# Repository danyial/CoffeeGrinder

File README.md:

# CoffeeGrinder

**Smart coffee grinder controller** with MQTT, OTA updates, and full Home Assistant integration.  
Includes 3D-printable housing, custom PCB (KiCad), and open-source firmware for ESP32.

---

## ✨ Features

- ☕️ Weight-based preset grinding
- 📡 MQTT auto-discovery (Home Assistant integration)
- 🌐 Web interface for configuration
- 🔧 Touch buttons for presets and calibration
- 📊 Live sensor telemetry and control
- 📦 STL files for 3D-printed case
- 🔌 KiCad schematics and PCB

---

## ⚙️ Cycloidal Drive (WIP)

This project uses a custom 3D-printed **cycloidal drive** to reduce the stepper motor's speed and increase torque.  
Currently, this mechanism is still under testing and may change in future iterations.

Contributions, feedback, and test results are welcome!

## 🖼️ Images

<p align="center">
  
  <br/>
  <em>CoffeeGrinder assembled</em>
</p>

<p align="center">
  
  <br/>
  <em>Section view (sliced)</em>
</p>

<p align="center">
  
  <br/>
  <em>Cycloidal Drive Top View</em>
</p>

<p align="center">
  
  <br/>
  <em>Cycloidal Drive Bottom View</em>
</p>

<p align="center">
  
  <br/>
  <em>Cycloidal Drive Sliced View</em>
</p>

<p align="center">

  <br/>
  <em>Home Assistant</em>
</p>

---

## 📁 Project Structure

```text
CoffeeGrinder/
├── src/                # Firmware source code
├── include/            # Header files
├── lib/                # Custom libraries (optional)
├── data/               # Web interface (SPIFFS)
├── hardware/
│   ├── stl/            # 3D-printable case parts
│   ├── kicad/          # KiCad PCB project
│   ├── images/         # Project images
│   └── docs/           # Rendered schematics (PDF)
├── docs/               # General project documentation
├── LICENSE.md          # License (AGPL + CC BY-NC-SA)
└── README.md           # This file
```

---

## 🚀 Getting Started

## 🧾 Bill of Materials (BOM)

> **Note**: Some of the links below are affiliate links. If you make a purchase through them, I may receive a small commission at no extra cost to you. Thank you for your support!

- Manual Coffee Grinder [🛒 Amazon](https://amzn.to/4o6IfON)
- ESP32 Dev Board [🛒 Amazon](https://amzn.to/40CVtJ8)
- OLED Display [🛒 Amazon](https://amzn.to/44N8UZx)
- Step Down Converter [🛒 Amazon](https://amzn.to/4o4rhAz)
- HX711 Weight Sensor [🛒 Amazon](https://amzn.to/4lEH1bS)
- Scale [🛒 Amazon](https://amzn.to/3Uswbtt)
- 3x TTP223 Touch Sensors [🛒 Amazon](https://amzn.to/4133kje)
- 3x 10nF Capacitors [🛒 Amazon](https://amzn.to/3IF0UBf)
- Brushless Motor 5010 360KV [🛒 Amazon](https://amzn.to/3VFhHHp)
- ESC 35A or similar (BLHeli_s) - any ESC for brushless motors should work [🛒 Amazon](https://amzn.to/4mAlXCX)
- 2x Bearing 30x37x4 [🛒 Amazon](https://amzn.to/46XXUtu)
- 2x Bearing 8x12x3.5 [🛒 Amazon](https://amzn.to/3UtORsR)
- 2x Bearing 7x13x4 [🛒 Amazon](https://amzn.to/470tUxc)
- 6x Spacer [🛒 Amazon](https://amzn.to/4lLxm3v)
- 12x Magnets 7x2 [🛒 Amazon](https://amzn.to/4f6ZivV)
- Power Supply [🛒 Amazon](https://amzn.to/4o3DJ3y)
- Elko [🛒 Amazon](https://amzn.to/3Uhur6B)
- DC Connector [🛒 Amazon](https://amzn.to/4f7ja2e)
- some cables
- 2x M3x12 SHCS screws [🛒 Amazon](https://amzn.to/4lT12eP)
- 6x M3x16 SHCS screws [🛒 Amazon](https://amzn.to/4lT12eP)
- 6x M3x25 SHCS screws [🛒 Amazon](https://amzn.to/4lT12eP)
- 10x M3x30 SHCS screws [🛒 Amazon](https://amzn.to/4lT12eP)
- 10x M3 screws [🛒 Amazon](https://amzn.to/44Lvy4o)
- 8x M3 nuts [🛒 Amazon](https://amzn.to/4lT12eP)
- 2x M4x20 SHCS screws [🛒 Amazon](https://amzn.to/4lILPgh)
- 6x M3 Threaded Inserts [🛒 Amazon](https://amzn.to/474Kj3K)
- 2x M4 Threaded Inserts [🛒 Amazon](https://amzn.to/44OBxFI)

### Requirements

- MQTT Broker (e.g., Mosquitto)
- Home Assistant (optional, for integration)

### Flashing

Use [PlatformIO](https://platformio.org/) in VSCode:

---

## 🔧 Web Interface

Accessible after WiFi configuration.  
Use it to set:

- MQTT server credentials
- Calibration
- Preset values
- Start grinding manually

---

## 🧠 Home Assistant Integration

Entities auto-discovered via MQTT:

- Sensors: weight, selected preset, scale factor, total weight
- Numbers: block threshold, preset weights
- Buttons: start, calibrate, tare, run preset

Make sure `discovery` is enabled in your MQTT integration.

---

## 🔐 License

- Firmware: [AGPL-3.0](https://www.gnu.org/licenses/agpl-3.0.html)
- Hardware + STL: [CC BY-NC-SA 4.0](https://creativecommons.org/licenses/by-nc-sa/4.0/)

**© 2025 Danny Smolinsky**

For commercial licensing inquiries, contact the author.

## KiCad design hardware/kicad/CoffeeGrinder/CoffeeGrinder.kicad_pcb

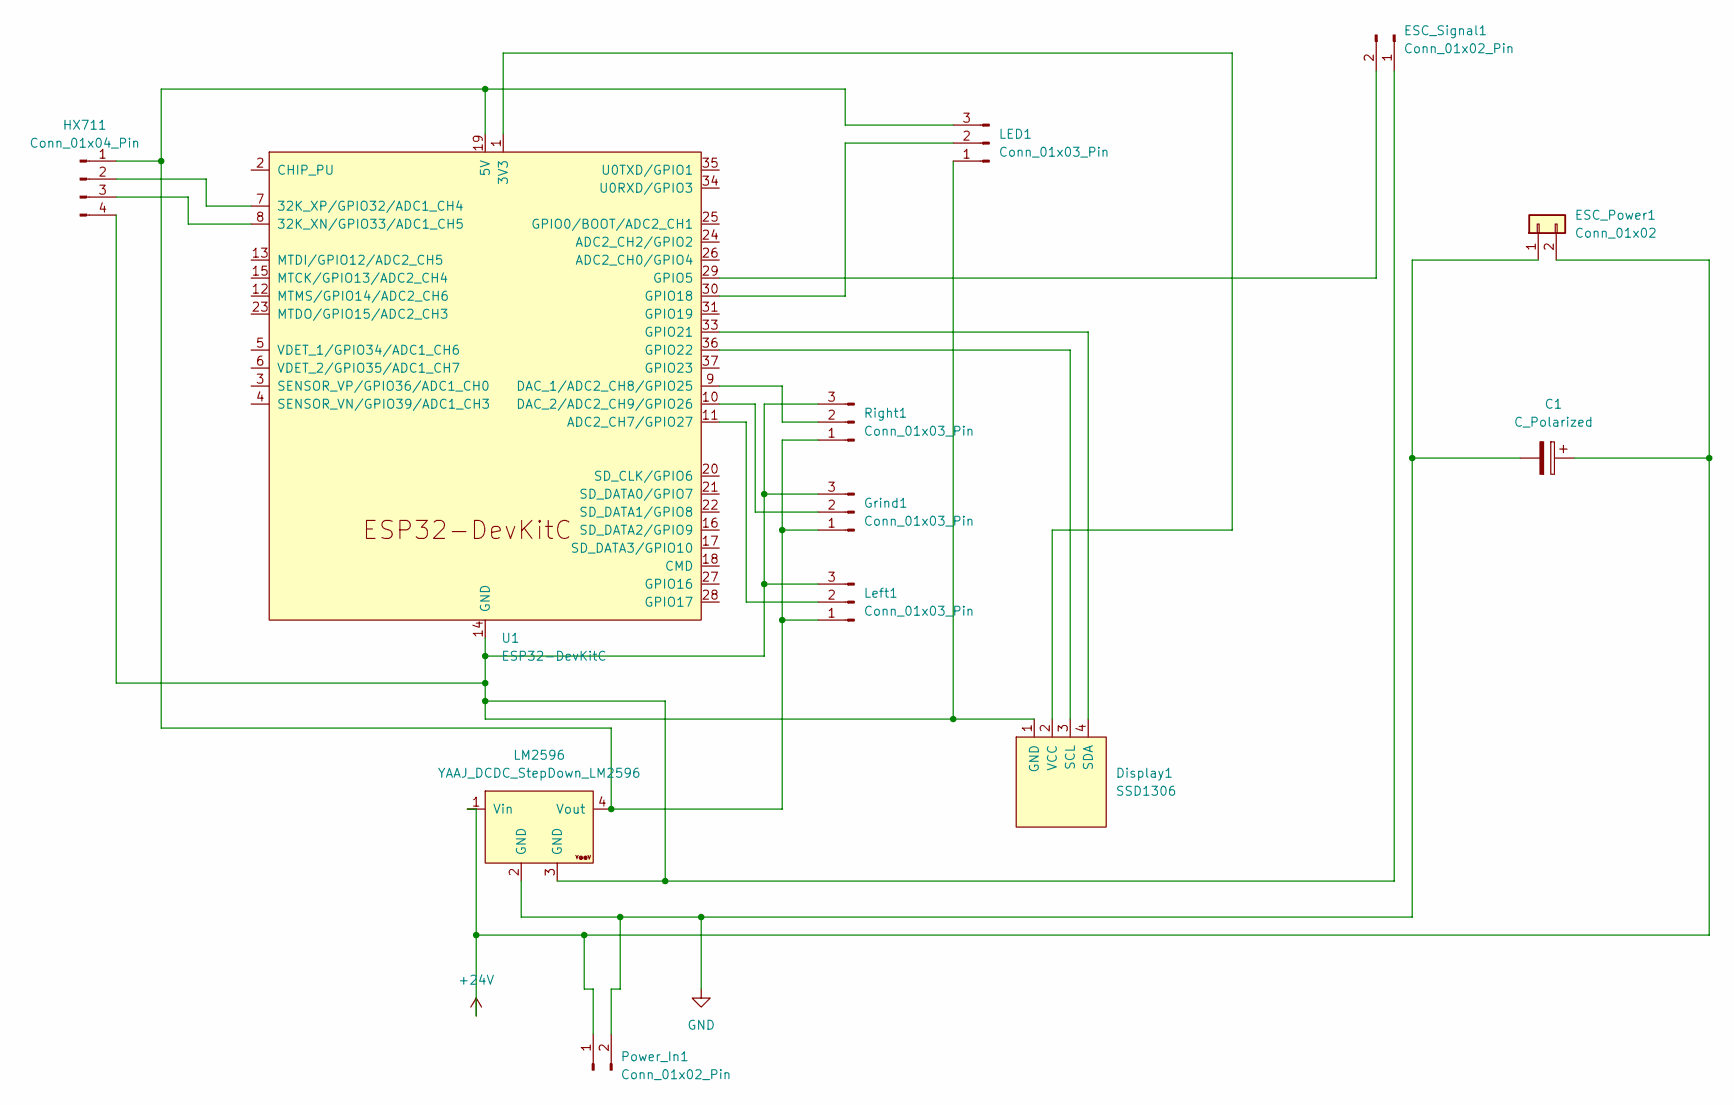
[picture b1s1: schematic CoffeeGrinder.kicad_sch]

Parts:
C1: C_Polarized; CP_Radial_D10.0mm_P7.50mm
Display1: SSD1306; JST_PH_B4B-PH-K_1x04_P2.00mm_Vertical
ESC_Power1: Conn_01x02; AMASS_XT30UPB-F_1x02_P5.0mm_Vertical
ESC_Signal1: Conn_01x02_Pin; JST_PH_B2B-PH-K_1x02_P2.00mm_Vertical
Grind1: Conn_01x03_Pin; JST_PH_B3B-PH-K_1x03_P2.00mm_Vertical
HX711: Conn_01x04_Pin; JST_PH_B4B-PH-K_1x04_P2.00mm_Vertical
LED1: Conn_01x03_Pin; JST_PH_B3B-PH-K_1x03_P2.00mm_Vertical
LM2596: YAAJ_DCDC_StepDown_LM2596
Left1: Conn_01x03_Pin; JST_PH_B3B-PH-K_1x03_P2.00mm_Vertical
Power_In1: Conn_01x02_Pin; AMASS_XT30UPB-M_1x02_P5.0mm_Vertical
Right1: Conn_01x03_Pin; JST_PH_B3B-PH-K_1x03_P2.00mm_Vertical
U1: ESP32-DevKitC

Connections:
+24V: C1.1, ESC_Power1.2, LM2596.1 (Vin), Power_In1.1
GND: C1.2, ESC_Power1.1, LM2596.2 (GND), Power_In1.2
unnamed: Display1.1 (GND), ESC_Signal1.1, Grind1.3, HX711.4, LED1.1, LM2596.3 (GND), Left1.3, Right1.3, U1.14 (GND), U1.32 (GND), U1.38 (GND)
unnamed: Display1.3 (SCL), U1.36 (GPIO22)
unnamed: Display1.4 (SDA), U1.33 (GPIO21)
unnamed: Display1.2 (VCC), U1.1 (3V3)
unnamed: ESC_Signal1.2, U1.29 (GPIO5)
unnamed: Grind1.1, HX711.1, LED1.3, LM2596.4 (Vout), Left1.1, Right1.1, U1.19 (5V)
unnamed: Grind1.2, U1.10 (DAC_2/ADC2_CH9/GPIO26)
unnamed: HX711.2, U1.7 (32K_XP/GPIO32/ADC1_CH4)
unnamed: HX711.3, U1.8 (32K_XN/GPIO33/ADC1_CH5)
unnamed: LED1.2, U1.30 (GPIO18)
unnamed: Left1.2, U1.11 (ADC2_CH7/GPIO27)
unnamed: Right1.2, U1.9 (DAC_1/ADC2_CH8/GPIO25)

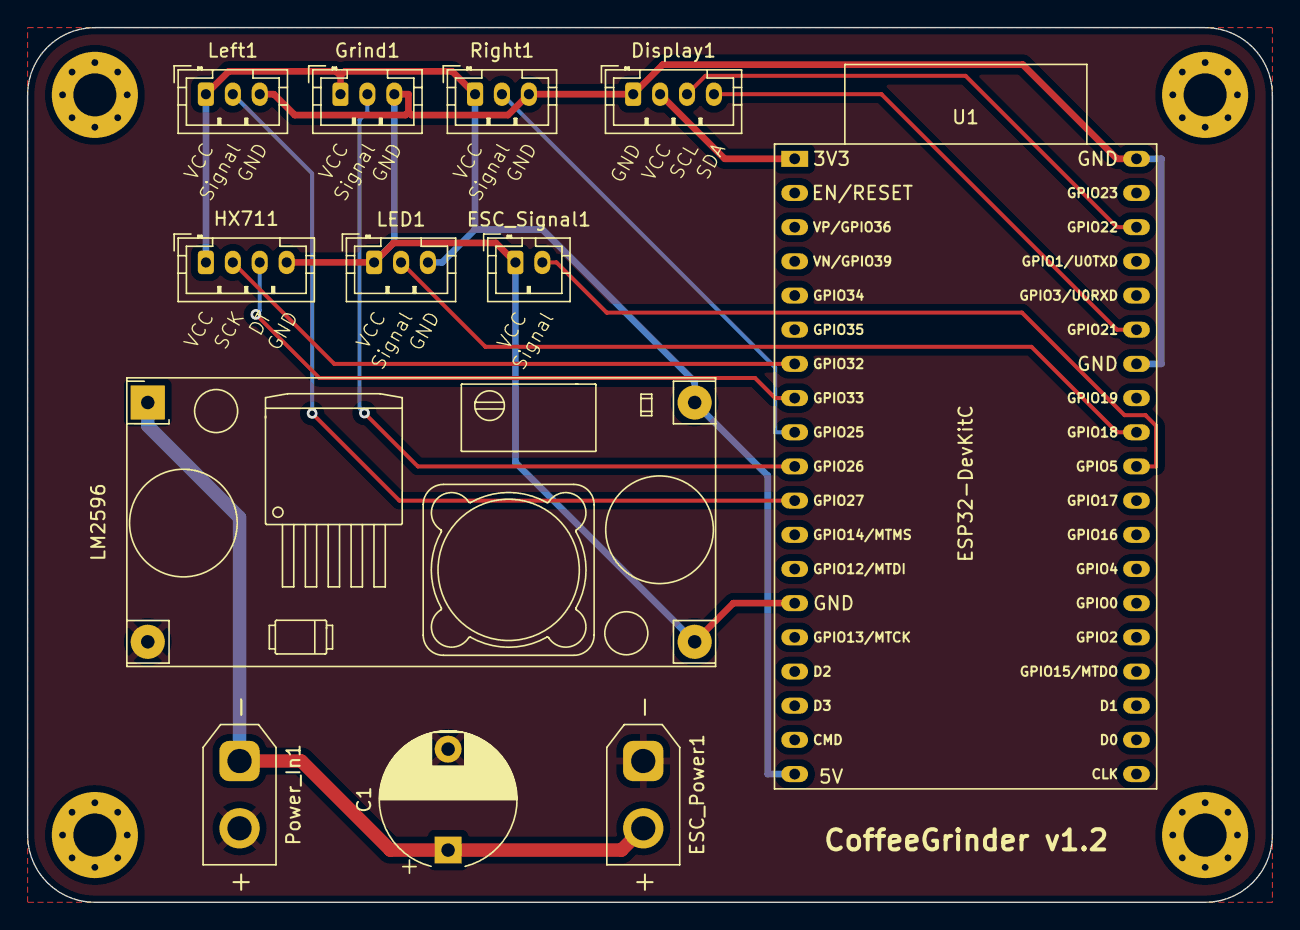
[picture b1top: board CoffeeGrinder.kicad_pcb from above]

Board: 2 copper layers, 92.5 x 65.0 mm, 16 parts (0 on the bottom side), 14 nets.

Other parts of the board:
REF1, REF2, REF3, REF4: MountingHole_3.2mm_M3_Pad_Via

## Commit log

2025-07-24 Add KiCAD files
2025-07-24 Add STLs
2025-07-24 Add Gerber Production files
2025-07-24 Add Images
2025-07-25 Rename some variables. Add description for cycloidal drive to readme
2025-07-25 Add Github Workflow
2025-07-25 Add MQTT identifier
2025-07-25 Fix Preset Counter
2025-07-25 Fix workflow
2025-07-25 Add version file
2025-07-25 v0.0.5
2025-07-25 v0.0.6
2025-07-25 v0.0.7
2025-07-25 v0.0.8
2025-07-25 Add Cycloidal Drive Images
2025-07-26 Fix blockThreshold not saved
2025-07-26 Add auto update to webinterface
2025-07-26 Revert auto update feature
2025-07-26 Fix selected preset not published on preset change
2025-07-26 Add weighing functionality. Fix publish config for HA
2025-07-29 Fix WiFi reconnection
2025-07-29 v0.0.15
2025-07-29 Fix scale taring
2025-07-30 Show remaining weight in RUNNING state. Update Images
2025-07-31 Add new Cycloidal Drive
2025-07-31 Fix: add scoped blocks in switch-case to prevent variable initialization warnings
    - Wrapped RUNNING case in braces to avoid "crosses initialization" warning
    - Improved stepper block detection logic using STEPPER_ROTATION
    - Ensured cleaner variable scope and safer direction handling
2025-07-31 Update BOM
2025-09-27 Replace stepper motor with 5010 brushless motor 360KV
2025-09-28 Version 0.0.20
2025-09-28 Add missing bowl STL
2025-09-28 Add missing motor mount. Update images
